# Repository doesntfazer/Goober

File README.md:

## Goober
The Goober is a Hummingbird-like layout.

There are several different versions of the Goober layout.
For firmware Check out the [Keyboard Dweebs Firmware Repositore](https://github.com/doesntfazer/Keyboard-Dweebs-Firmware-repository)

## Goober Original

This keyboard is hot-swap, runs on rp2040 zero.
## Goobertrax

This keyboard is hot-swap, runs on rp2040 zero, and has a PMW3360 sensor trackball
## Goobertrax-e

This keyboard is hot-swap, runs on rp2040 zero, and has a PMW3360 sensor trackball. Additionally, it has 2 Panasonic rotary encoders, and 3 extra keys for mouse buttons
## CHore

This keyboard runs on FAK firmware, and is powered by a CH552G microcontroller.
## Goober CHOC

Same as original but with slightly different layout, and it is Choc Spaced.
## Goober-wi
No image available yet. Split wireless Goober.

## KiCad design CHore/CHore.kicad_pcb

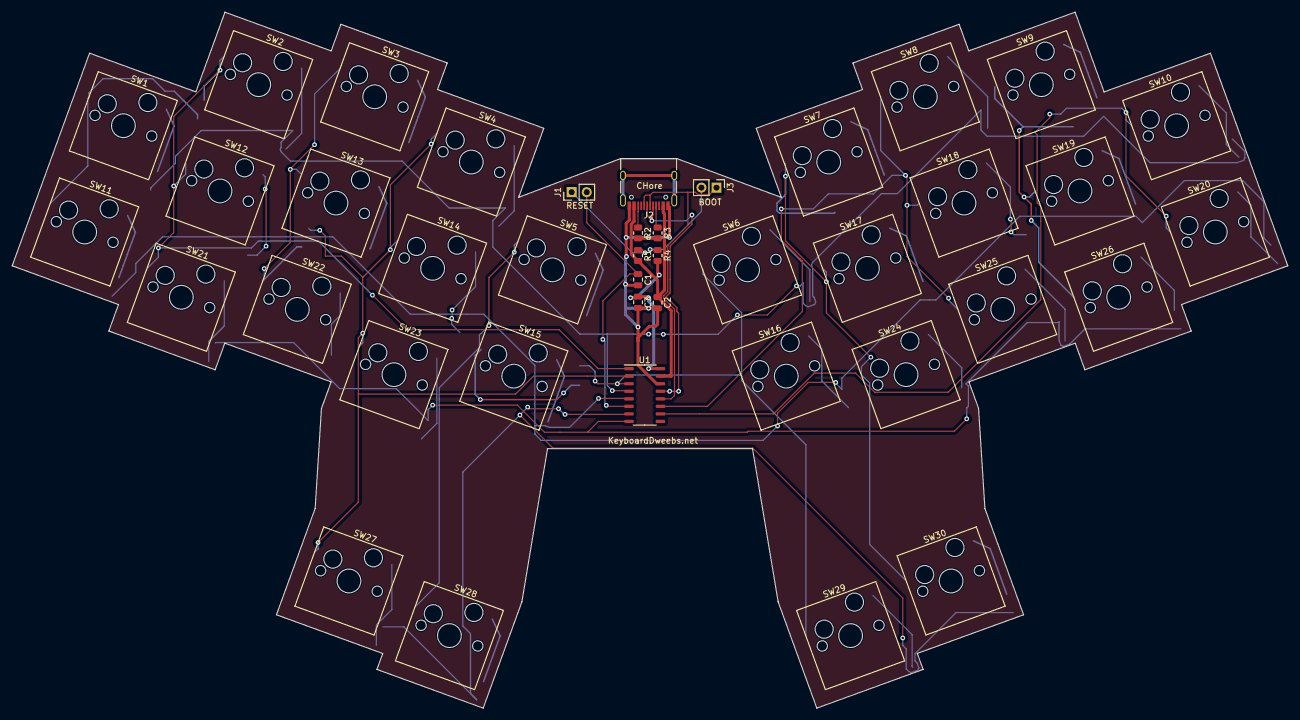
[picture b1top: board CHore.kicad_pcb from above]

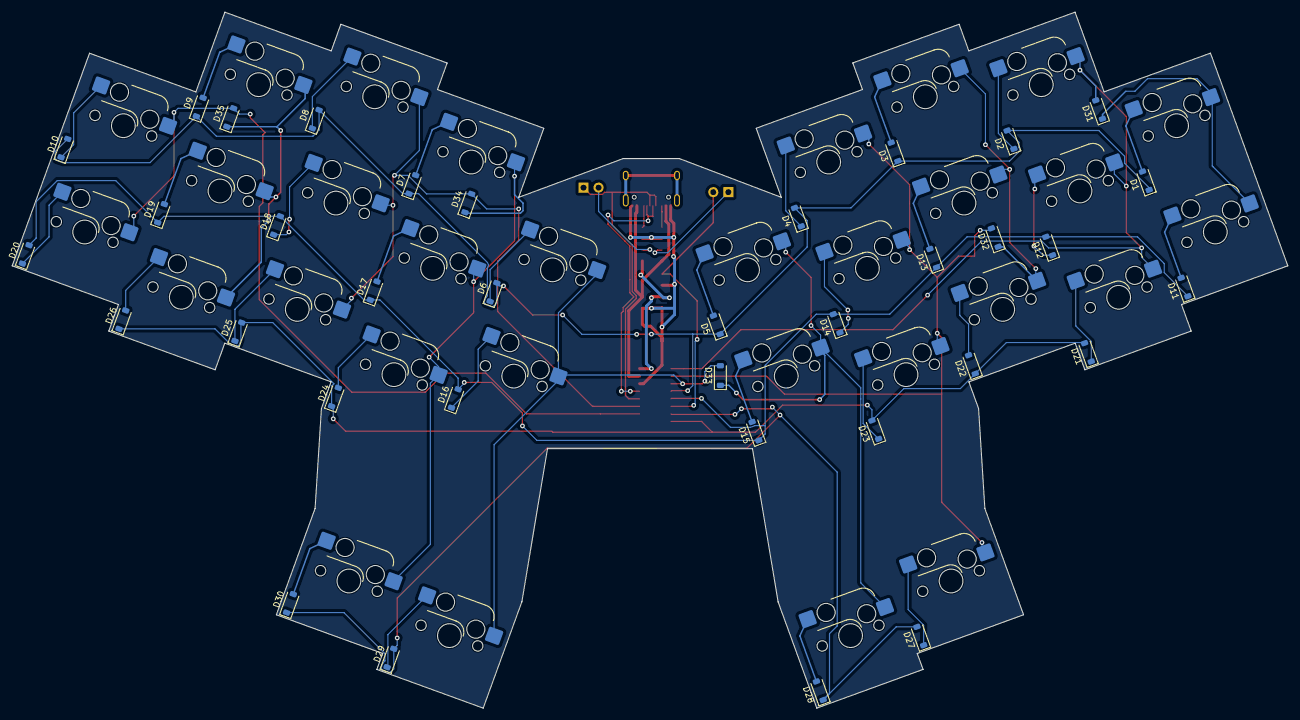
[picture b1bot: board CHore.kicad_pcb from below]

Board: 2 copper layers, 214.8 x 117.2 mm, 76 parts (35 on the bottom side), 54 nets.

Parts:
C1, C2, C3: 100n; C_0805_2012Metric
D1, D2, D3, D4, D5, D6, D7, D8, D9, D10, D11, D12, D13, D14, D15, D16, D17, D18, D19, D20, D21, D22, D23, D24, D25, D26, D27, D28, D29, D30, D31, D32, D33, D34, D35: 1N4148W; D_SOD-123
J1, J3: Conn_01x02_Pin; PinHeader_1x02_P2.54mm_Vertical
J2: USB_C_Receptacle_USB2.0; USB_C_Receptacle_HRO_TYPE-C-31-M-12
R1: 330R; R_0805_2012Metric
R2, R3: 5.1k; R_0805_2012Metric
R4: 10K; R_0805_2012Metric
SW1, SW2, SW3, SW4, SW5, SW6, SW7, SW8, SW9, SW10, SW11, SW12, SW13, SW14, SW15, SW16, SW17, SW18, SW19, SW20, SW21, SW22, SW23, SW24, SW25, SW26, SW27, SW28, SW29, SW30: SW_PUSH; SW_Hotswap_Kailh_MX_1.00u
U1: CH552G; STC_SOP-16_3.9x9.9mm_P1.27mm

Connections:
/3V3: C3.1, R4.2, U1.16 (V33)
/5v: C2.1, J2.A4 (VBUS), J2.A9 (VBUS), J2.B4 (VBUS), J2.B9 (VBUS), R1.2, U1.15 (VCC/VDD)
/COL0: D31.2 (A), SW2.1, SW12.1, SW21.1, U1.1 (P3.2/TXD1_/INT0/VBUS1/AIN3)
/COL1: D32.2 (A), SW4.1, SW14.1, SW23.1, SW27.1, U1.2 (P1.4/T2_/CAP1_/SCS/TIN2/UCC1/AIN1)
/COL2: D33.2 (A), SW6.1, SW16.1, SW29.1, U1.3 (P1.5/MOSI/PWM1/TIN3/UCC2/AIN2)
/COL3: D34.2 (A), SW8.1, SW18.1, SW25.1, U1.11 (P3.4/PWM2/RXD1_/T0)
/COL4: D35.2 (A), SW10.1, SW20.1, U1.10 (P3.3/INT1)
/DATA+: J2.A6 (D+), J2.B6 (D+), J3.1, U1.12 (P3.6/UDP)
/DATA-: J2.A7 (D-), J2.B7 (D-), U1.13 (P3.7/UDM)
/GND: C1.2, C2.2, C3.2, J2.A1 (GND), J2.A12 (GND), J2.B1 (GND), J2.B12 (GND), R2.2, R3.2, U1.14 (GND/VSS)
/RESET: C1.1, J1.2, U1.6 (RST/T2EX_/CAP2_)
/ROW0: D1.1 (K), D2.2 (A), D3.1 (K), D4.2 (A), D5.1 (K), D6.2 (A), D7.1 (K), D8.2 (A), D9.1 (K), D10.2 (A), U1.4 (P1.6/MISO/RXD1/TIN4)
/ROW1: D11.1 (K), D12.2 (A), D13.1 (K), D14.2 (A), D15.1 (K), D16.2 (A), D17.1 (K), D18.2 (A), D19.1 (K), D20.2 (A), U1.5 (P1.7/SCK/TXD1/TIN5)
/ROW2: D21.2 (A), D22.1 (K), D23.2 (A), D24.1 (K), D25.2 (A), D26.1 (K), U1.8 (P3.0/PWM1_/RXD)
/ROW3: D27.2 (A), D28.1 (K), D29.2 (A), D30.1 (K), U1.7 (P3.1/PWM2_/TXD)
unnamed: D1.2 (A), SW1.2
unnamed: D2.1 (K), SW2.2
unnamed: D3.2 (A), SW3.2
unnamed: D4.1 (K), SW4.2
unnamed: D5.2 (A), SW5.2
unnamed: D6.1 (K), SW6.2
unnamed: D7.2 (A), SW7.2
unnamed: D8.1 (K), SW8.2
unnamed: D9.2 (A), SW9.2
unnamed: D10.1 (K), SW10.2
unnamed: D11.2 (A), SW11.2
unnamed: D12.1 (K), SW12.2
unnamed: D13.2 (A), SW13.2
unnamed: D14.1 (K), SW14.2
unnamed: D15.2 (A), SW15.2
unnamed: D16.1 (K), SW16.2
unnamed: D17.2 (A), SW17.2
unnamed: D18.1 (K), SW18.2
unnamed: D19.2 (A), SW19.2
unnamed: D20.1 (K), SW20.2
unnamed: D21.1 (K), SW21.2
unnamed: D22.2 (A), SW22.2
unnamed: D23.1 (K), SW23.2
unnamed: D24.2 (A), SW24.2
unnamed: D25.1 (K), SW25.2
unnamed: D26.2 (A), SW26.2
unnamed: D27.1 (K), SW27.2
unnamed: D28.2 (A), SW28.2
unnamed: D29.1 (K), SW29.2
unnamed: D30.2 (A), SW30.2
unnamed: D31.1 (K), SW1.1, SW11.1
unnamed: D32.1 (K), SW3.1, SW13.1, SW22.1
unnamed: D33.1 (K), SW5.1, SW15.1, SW28.1
unnamed: D34.1 (K), SW7.1, SW17.1, SW24.1, SW30.1
unnamed: D35.1 (K), SW9.1, SW19.1, SW26.1
unnamed: J1.1, R1.1
unnamed: J2.A5 (CC1), R3.1
unnamed: J2.B5 (CC2), R2.1
unnamed: J3.2, R4.1

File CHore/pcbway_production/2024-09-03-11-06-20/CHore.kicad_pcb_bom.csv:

Designator,Quantity,Value,Footprint,Package,MPN,Mount_Type
"C1, C2, C3",3,100n,C_0805_2012Metric,,,smt
"D1, D10, D11, D12, D13, D14, D15, D16, D17, D18, D19, D2, D20, D21, D22, D23, D24, D25, D26, D27, D28, D29, D3, D30, D4, D5, D6, D7, D8, D9",30,1N4148W,D_SOD-123,,,smt
"J1, J3",2,Conn_01x02_Pin,PinHeader_1x02_P2.54mm_Vertical,,,tht
J2,1,USB_C_Receptacle_USB2.0,USB_C_Receptacle_HRO_TYPE-C-31-M-12,,,smt
R1,1,330R,R_0805_2012Metric,,,smt
"R2, R3",2,5.1k,R_0805_2012Metric,,,smt
R4,1,10K,R_0805_2012Metric,,,smt
"R5, R6, R7, R8, R9",5,10k,R_0603_1608Metric,,,smt
"SW1, SW10, SW11, SW12, SW13, SW14, SW15, SW16, SW17, SW18, SW19, SW2, SW20, SW21, SW22, SW23, SW24, SW25, SW26, SW27, SW28, SW29, SW3, SW30, SW4, SW5, SW6, SW7, SW8, SW9",30,SW_PUSH,SW_Hotswap_Kailh_MX_1.00u,,,smt
U1,1,CH552G,STC_SOP-16_3.9x9.9mm_P1.27mm,,,smt

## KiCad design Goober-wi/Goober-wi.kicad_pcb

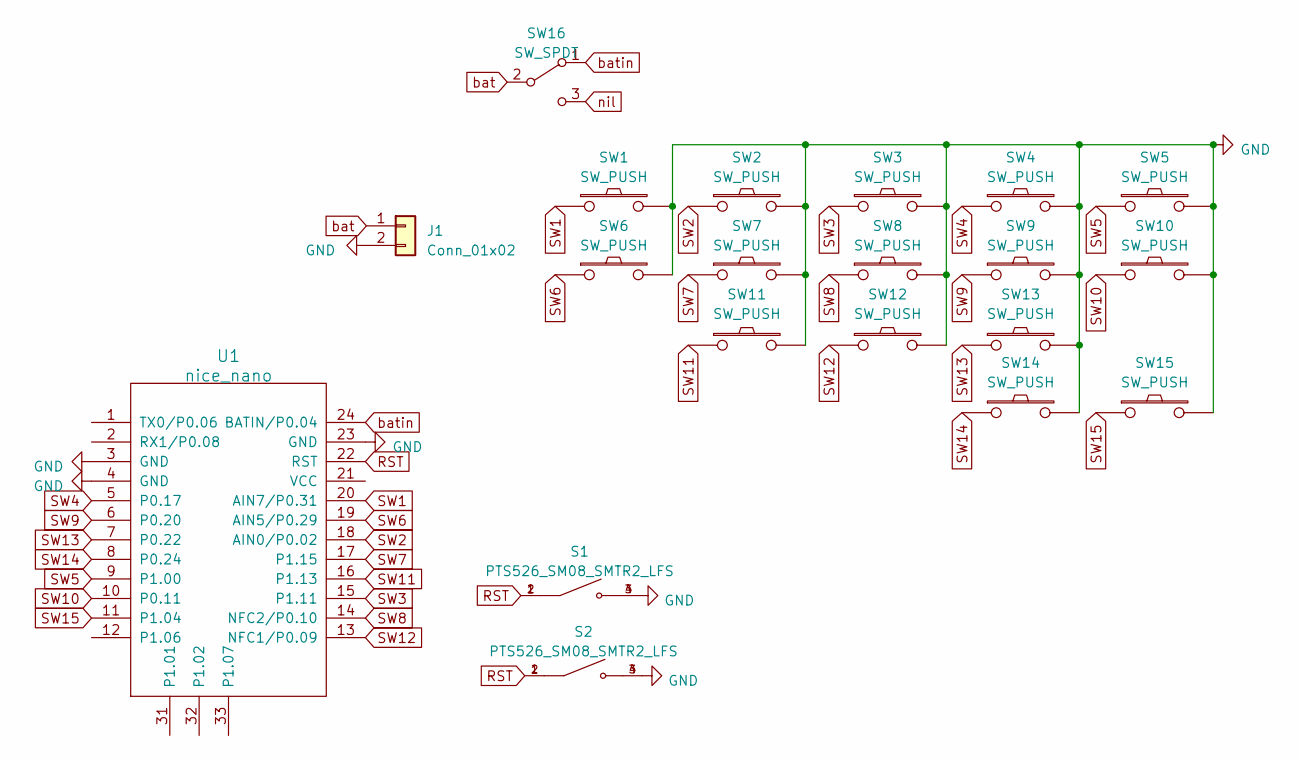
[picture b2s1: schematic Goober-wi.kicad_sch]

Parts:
J1: Conn_01x02; PinHeader_1x02_P2.54mm_Vertical
S1, S2: PTS526_SM08_SMTR2_LFS; SW_PTS526_SM08_SMTR2_LFS; PARTREV 20 mar 19
SW1, SW2, SW3, SW4, SW5, SW6, SW7, SW8, SW9, SW10, SW11, SW12, SW13, SW14, SW15: SW_PUSH; SW_Kailh_Choc_V1V2_1.00u - Reversable
SW16: SW_SPDT; switch-MSK-12C02-smd
U1: nice_nano

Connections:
GND: J1.2, S1.3, S1.4, S2.3, S2.4, SW1.2, SW2.2, SW3.2, SW4.2, SW5.2, SW6.2, SW7.2, SW8.2, SW9.2, SW10.2, SW11.2, SW12.2, SW13.2, SW14.2, SW15.2, U1.3 (GND), U1.4 (GND), U1.23 (GND)
RST: S1.1, S1.2, S2.1, S2.2, U1.22 (RST)
SW1: SW1.1, U1.20 (AIN7/P0.31)
SW2: SW2.1, U1.18 (AIN0/P0.02)
SW3: SW3.1, U1.15 (P1.11)
SW4: SW4.1, U1.5 (P0.17)
SW5: SW5.1, U1.9 (P1.00)
SW6: SW6.1, U1.19 (AIN5/P0.29)
SW7: SW7.1, U1.17 (P1.15)
SW8: SW8.1, U1.14 (NFC2/P0.10)
SW9: SW9.1, U1.6 (P0.20)
SW10: SW10.1, U1.10 (P0.11)
SW11: SW11.1, U1.16 (P1.13)
SW12: SW12.1, U1.13 (NFC1/P0.09)
SW13: SW13.1, U1.7 (P0.22)
SW14: SW14.1, U1.8 (P0.24)
SW15: SW15.1, U1.11 (P1.04)
bat: J1.1, SW16.2 (B)
batin: SW16.1 (A), U1.24 (BATIN/P0.04)
nil: SW16.3 (C)

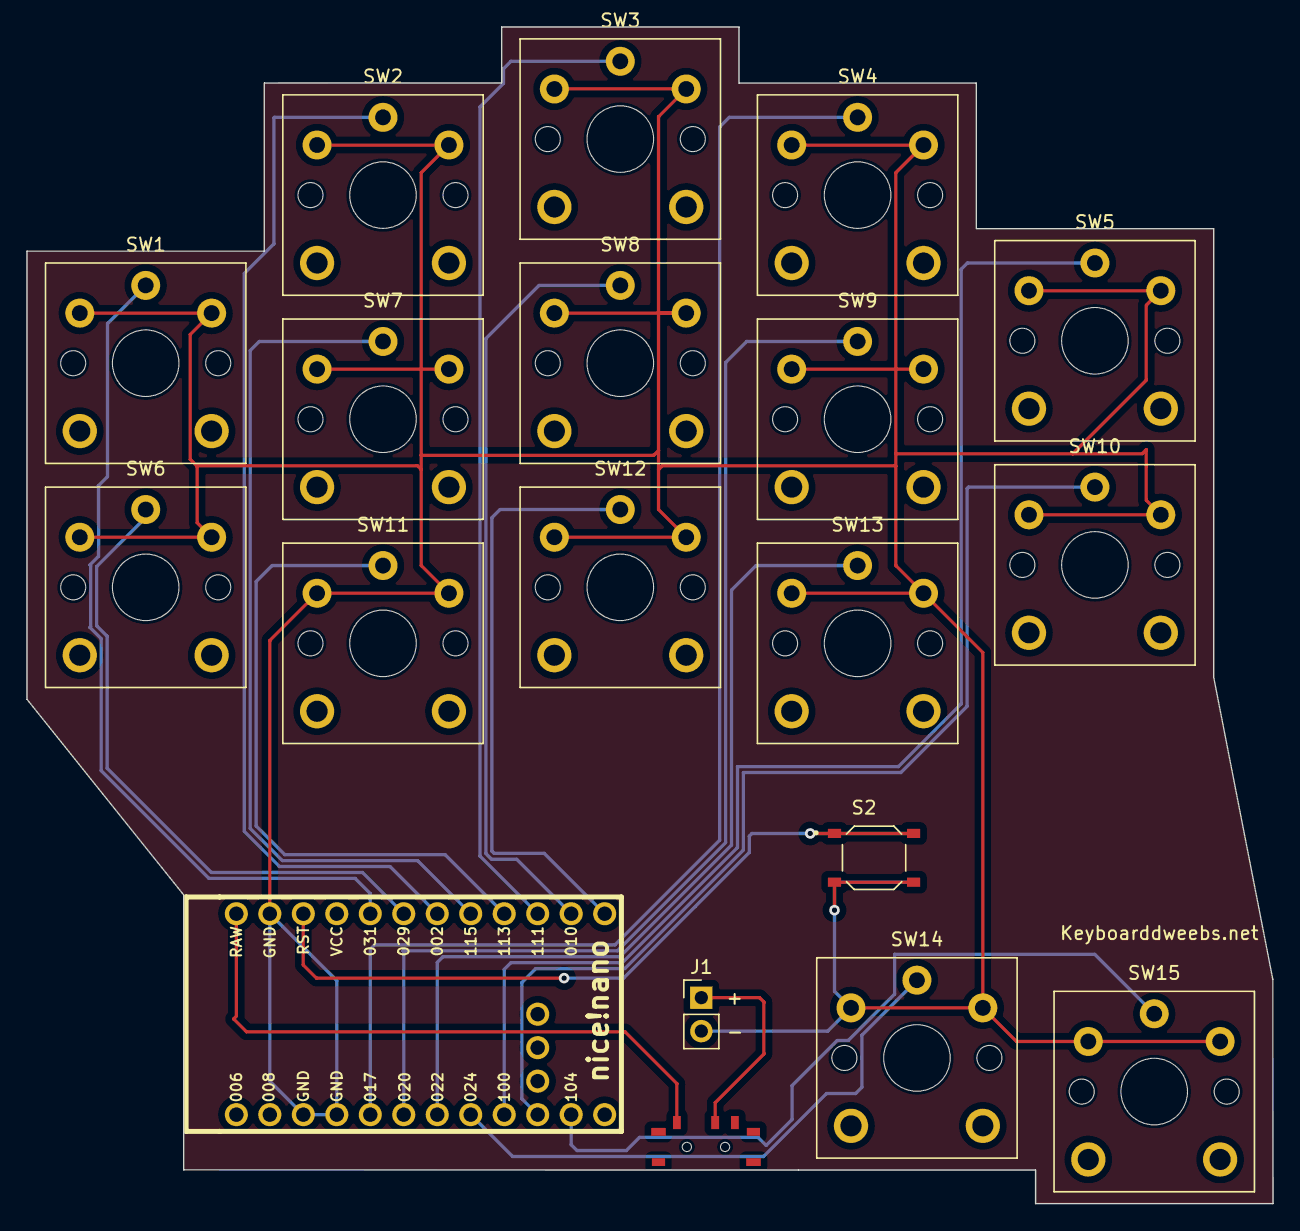
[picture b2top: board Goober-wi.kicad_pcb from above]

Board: 2 copper layers, 94.5 x 89.2 mm, 20 parts (1 on the bottom side), 19 nets.

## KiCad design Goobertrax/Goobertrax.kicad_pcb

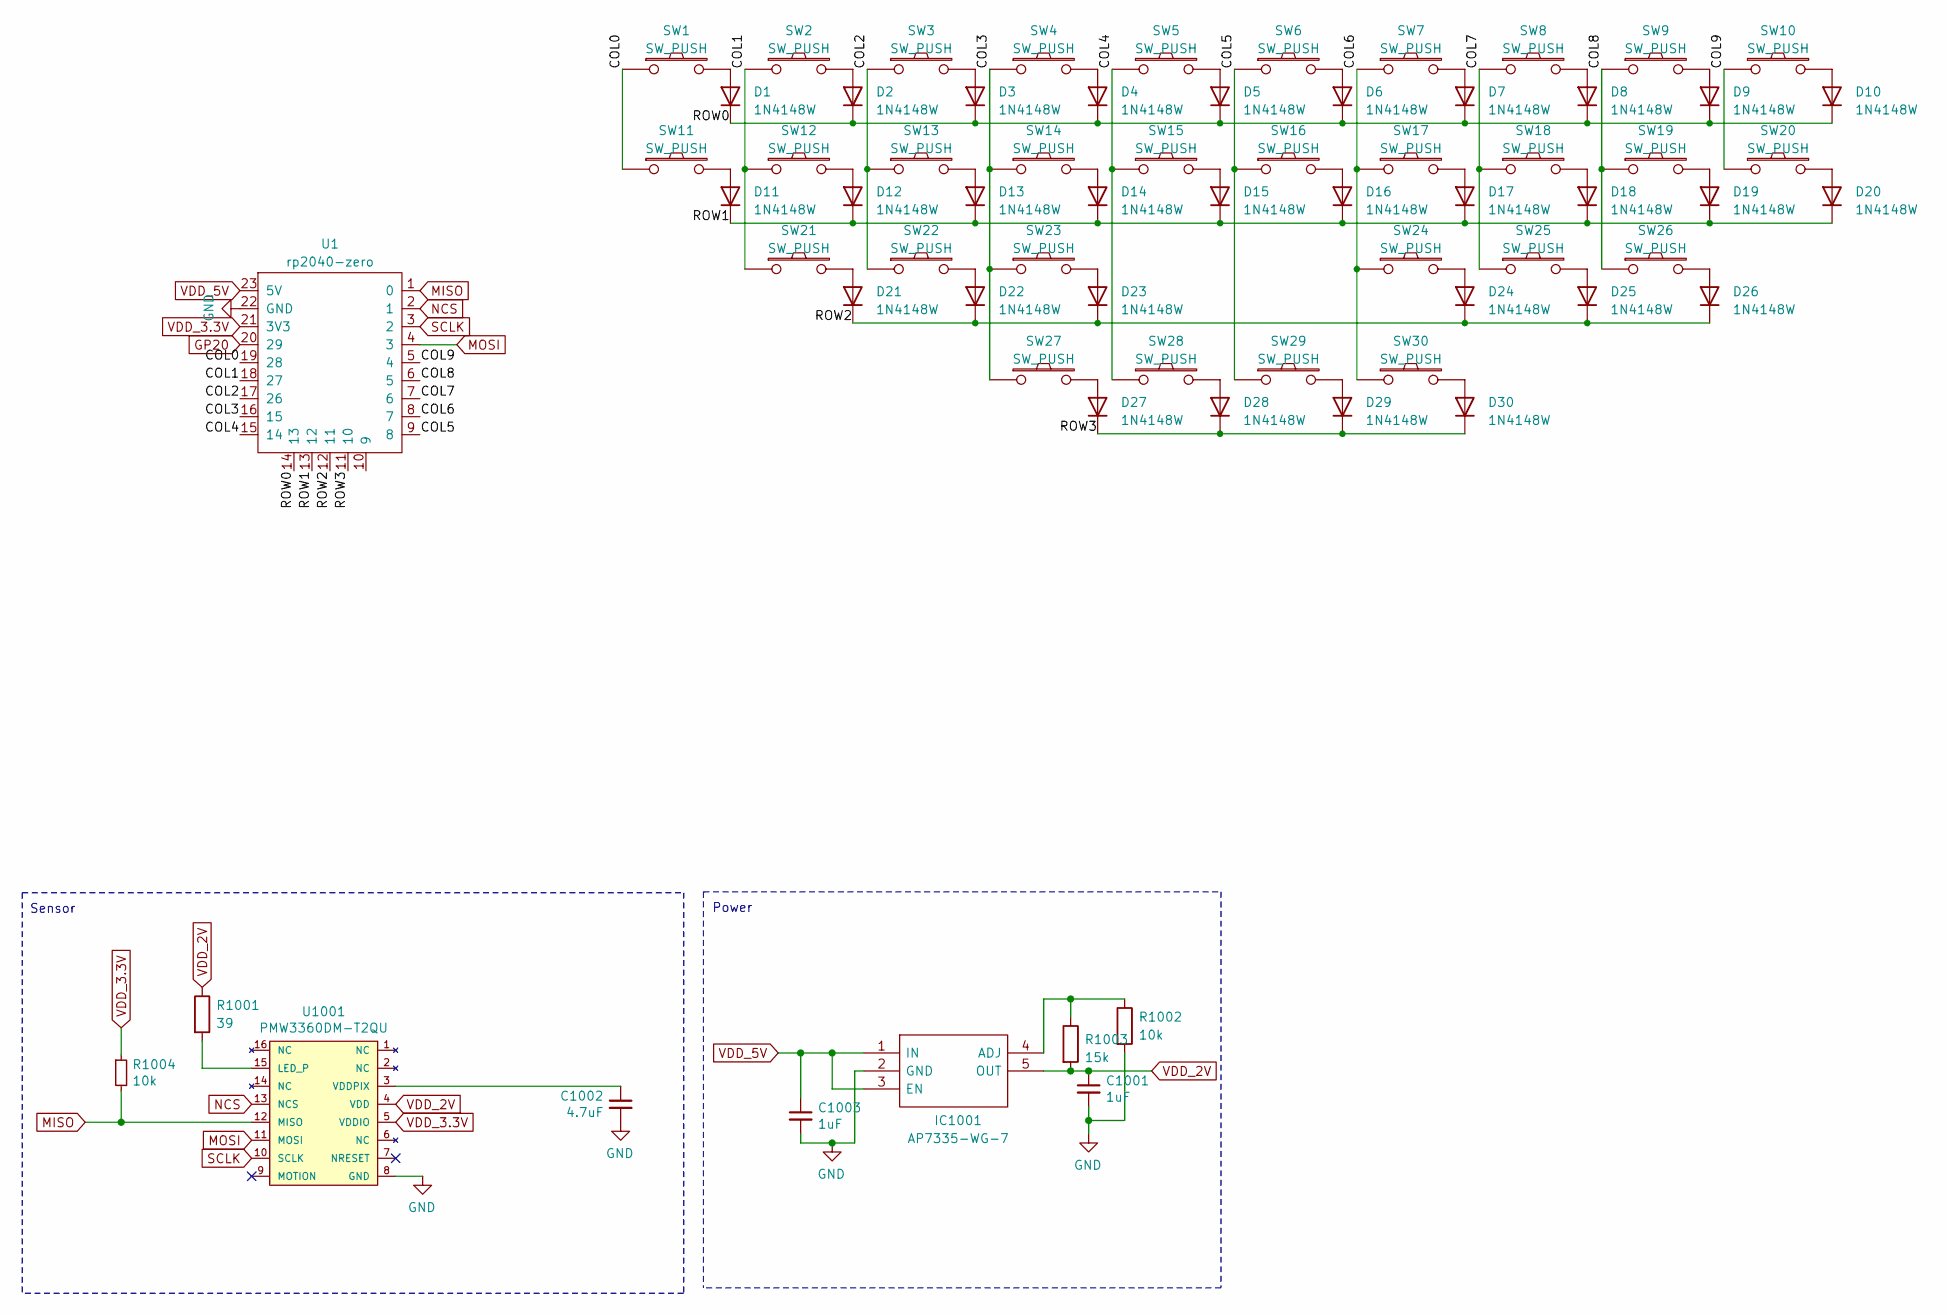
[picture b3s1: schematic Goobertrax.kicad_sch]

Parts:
C1001, C1003: 1uF; C_0603_1608Metric; LCSC C15849
C1002: 4.7uF; C_0603_1608Metric; LCSC C19666
D1, D2, D3, D4, D5, D6, D7, D8, D9, D10, D11, D12, D13, D14, D15, D16, D17, D18, D19, D20, D21, D22, D23, D24, D25, D26, D27, D28, D29, D30: 1N4148W; D_SOD-123
IC1001: AP7335-WG-7; SOT-23-5_HandSoldering; Manufacturer_Part_Number AP7331-WG-7; Mouser Part Number 621-AP7331-WG-7
R1001: 39; R_0603_1608Metric; LCSC C23154
R1002, R1004: 10k; R_0603_1608Metric; LCSC C25804
R1003: 15k; R_0603_1608Metric; LCSC C22809
SW1, SW2, SW3, SW4, SW5, SW6, SW7, SW8, SW9, SW10, SW11, SW12, SW13, SW14, SW15, SW16, SW17, SW18, SW19, SW20, SW21, SW22, SW23, SW24, SW25, SW26, SW27, SW28, SW29, SW30: SW_PUSH; SW_Hotswap_Kailh_MX_1.00u
U1: rp2040-zero; rp2040-zero-tht-nocut-largerpads
U1001: PMW3360DM-T2QU; DIP-16_W10.16mm

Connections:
/COL0: SW1.1, SW11.1, U1.19 (28)
/COL1: SW2.1, SW12.1, SW21.1, U1.18 (27)
/COL2: SW3.1, SW13.1, SW22.1, U1.17 (26)
/COL3: SW4.1, SW14.1, SW23.1, SW27.1, U1.16 (15)
/COL4: SW5.1, SW15.1, SW28.1, U1.15 (14)
/COL5: SW6.1, SW16.1, SW29.1, U1.9 (8)
/COL6: SW7.1, SW17.1, SW24.1, SW30.1, U1.8 (7)
/COL7: SW8.1, SW18.1, SW25.1, U1.7 (6)
/COL8: SW9.1, SW19.1, SW26.1, U1.6 (5)
/COL9: SW10.1, SW20.1, U1.5 (4)
/ROW0: D1.1 (K), D2.1 (K), D3.1 (K), D4.1 (K), D5.1 (K), D6.1 (K), D7.1 (K), D8.1 (K), D9.1 (K), D10.1 (K), U1.14 (13)
/ROW1: D11.1 (K), D12.1 (K), D13.1 (K), D14.1 (K), D15.1 (K), D16.1 (K), D17.1 (K), D18.1 (K), D19.1 (K), D20.1 (K), U1.13 (12)
/ROW2: D21.1 (K), D22.1 (K), D23.1 (K), D24.1 (K), D25.1 (K), D26.1 (K), U1.12 (11)
/ROW3: D27.1 (K), D28.1 (K), D29.1 (K), D30.1 (K), U1.11 (10)
GND: C1001.2, C1002.2, C1003.2, IC1001.2 (GND), R1002.2, U1.22 (GND), U1001.8 (GND)
MISO: R1004.2, U1.1 (0), U1001.12 (MISO)
MOSI: U1.4 (3), U1001.11 (MOSI)
NCS: U1.2 (1), U1001.13 (NCS)
unnamed: D1.2 (A), SW1.2
unnamed: D2.2 (A), SW2.2
unnamed: D3.2 (A), SW3.2
unnamed: D4.2 (A), SW4.2
unnamed: D5.2 (A), SW5.2
unnamed: D6.2 (A), SW6.2
unnamed: D7.2 (A), SW7.2
unnamed: D8.2 (A), SW8.2
unnamed: D9.2 (A), SW9.2
unnamed: D10.2 (A), SW10.2
unnamed: D11.2 (A), SW11.2
unnamed: D12.2 (A), SW12.2
unnamed: D13.2 (A), SW13.2
unnamed: D14.2 (A), SW14.2
unnamed: D15.2 (A), SW15.2
unnamed: D16.2 (A), SW16.2
unnamed: D17.2 (A), SW17.2
unnamed: D18.2 (A), SW18.2
unnamed: D19.2 (A), SW19.2
unnamed: D20.2 (A), SW20.2
unnamed: D21.2 (A), SW21.2
unnamed: D22.2 (A), SW22.2
unnamed: D23.2 (A), SW23.2
unnamed: D24.2 (A), SW24.2
unnamed: D25.2 (A), SW25.2
unnamed: D26.2 (A), SW26.2
unnamed: D27.2 (A), SW27.2
unnamed: D28.2 (A), SW28.2
unnamed: D29.2 (A), SW29.2
unnamed: D30.2 (A), SW30.2
unnamed: IC1001.4 (ADJ), R1002.1, R1003.1
unnamed: R1001.2, U1001.15 (LED_P)
unnamed: C1002.1, U1001.3 (VDDPIX)
SCLK: U1.3 (2), U1001.10 (SCLK)
VDD_2V: C1001.1, IC1001.5 (OUT), R1001.1, R1003.2, U1001.4 (VDD)
VDD_3.3V: R1004.1, U1.21 (3V3), U1001.5 (VDDIO)
VDD_5V: C1003.1, IC1001.1 (IN), IC1001.3 (EN), U1.23 (5V)

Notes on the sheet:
Power
Sensor

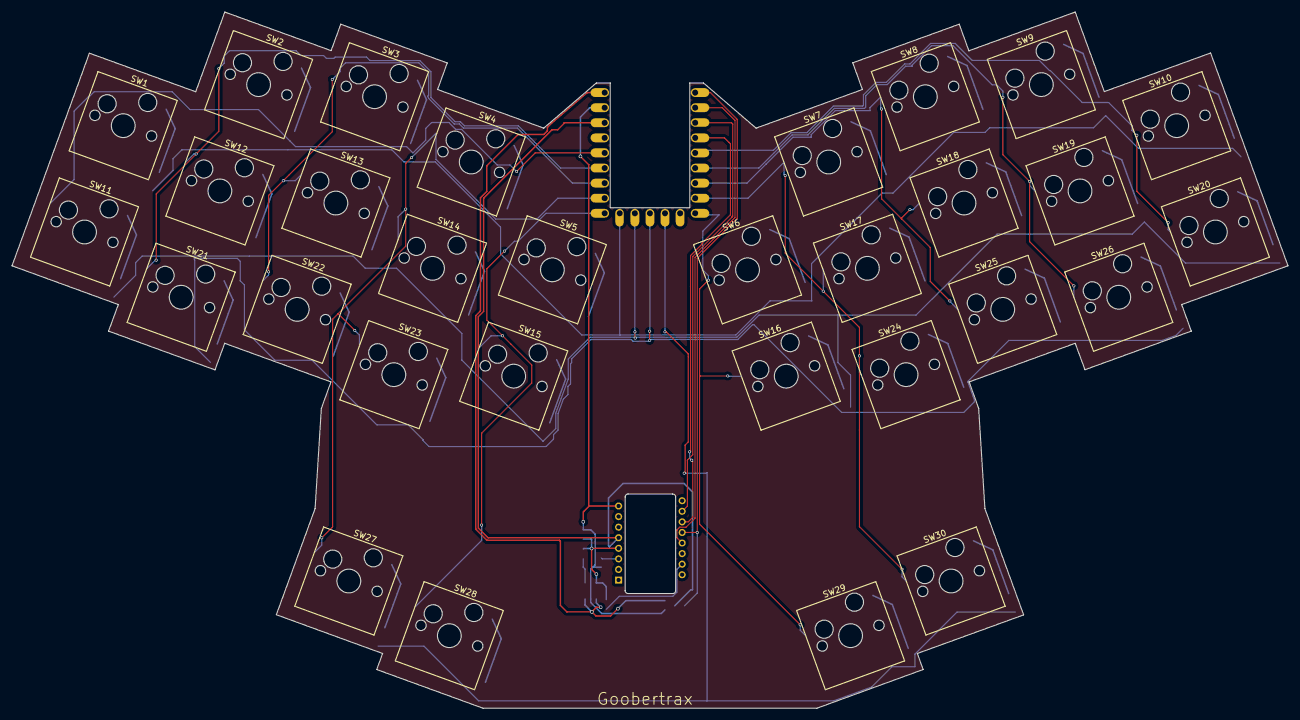
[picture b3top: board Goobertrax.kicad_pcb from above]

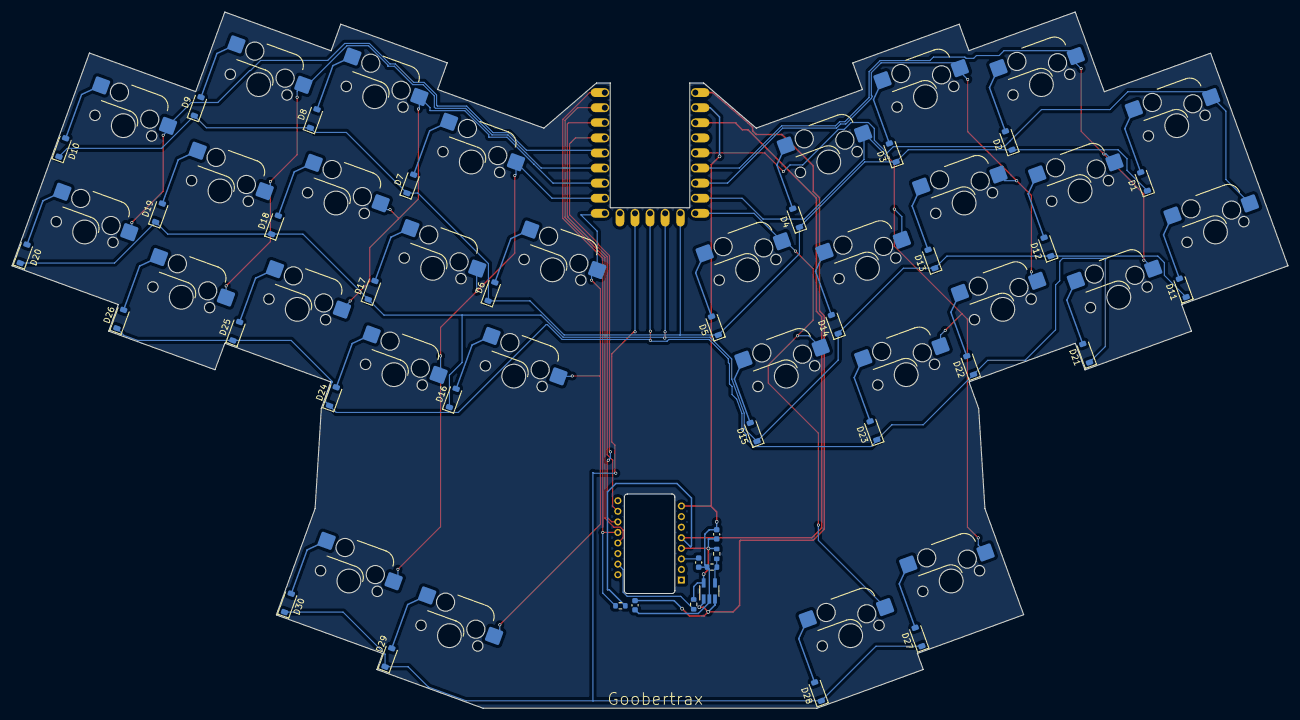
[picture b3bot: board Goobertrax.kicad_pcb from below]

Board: 2 copper layers, 214.8 x 117.2 mm, 70 parts (39 on the bottom side), 55 nets.

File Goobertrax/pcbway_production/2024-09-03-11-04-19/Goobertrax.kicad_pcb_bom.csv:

Designator,Quantity,Value,Footprint,Package,MPN,Mount_Type
"C1001, C1003",2,1uF,C_0603_1608Metric,,,smt
C1002,1,4.7uF,C_0603_1608Metric,,,smt
"D1, D10, D11, D12, D13, D14, D15, D16, D17, D18, D19, D2, D20, D21, D22, D23, D24, D25, D26, D27, D28, D29, D3, D30, D4, D5, D6, D7, D8, D9",30,1N4148W,D_SOD-123,,,smt
IC1001,1,AP7335-WG-7,SOT-23-5_HandSoldering,,AP7331-WG-7,smt
R1001,1,39,R_0603_1608Metric,,,smt
"R1002, R1004",2,10k,R_0603_1608Metric,,,smt
R1003,1,15k,R_0603_1608Metric,,,smt
"SW1, SW10, SW11, SW12, SW13, SW14, SW15, SW16, SW17, SW18, SW19, SW2, SW20, SW21, SW22, SW23, SW24, SW25, SW26, SW27, SW28, SW29, SW3, SW30, SW4, SW5, SW6, SW7, SW8, SW9",30,SW_PUSH,SW_Hotswap_Kailh_MX_1.00u,,,smt
U1,1,rp2040-zero,rp2040-zero-tht-nocut-largerpads,,,tht
U1001,1,PMW3360DM-T2QU,DIP-16_W10.16mm,,,tht

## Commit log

2024-07-26 added pcb pics
2024-08-05 Added 3d Case files.
2024-09-03 Reorganized, Added additional boards
    Added Goobertrax, Goobertrax-e, CHore, and GooberCHOC.
2024-09-03 Added Goober-wi
2024-09-03 Created Readme
2024-09-03 fixed readme.md and added more assets
2024-09-03 Fixed hardware to prevent ghosting.
2024-09-05 Removed extra files

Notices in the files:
Goobertrax/Goobertrax.kicad_sch:
Copyright Quentin Lebastard
